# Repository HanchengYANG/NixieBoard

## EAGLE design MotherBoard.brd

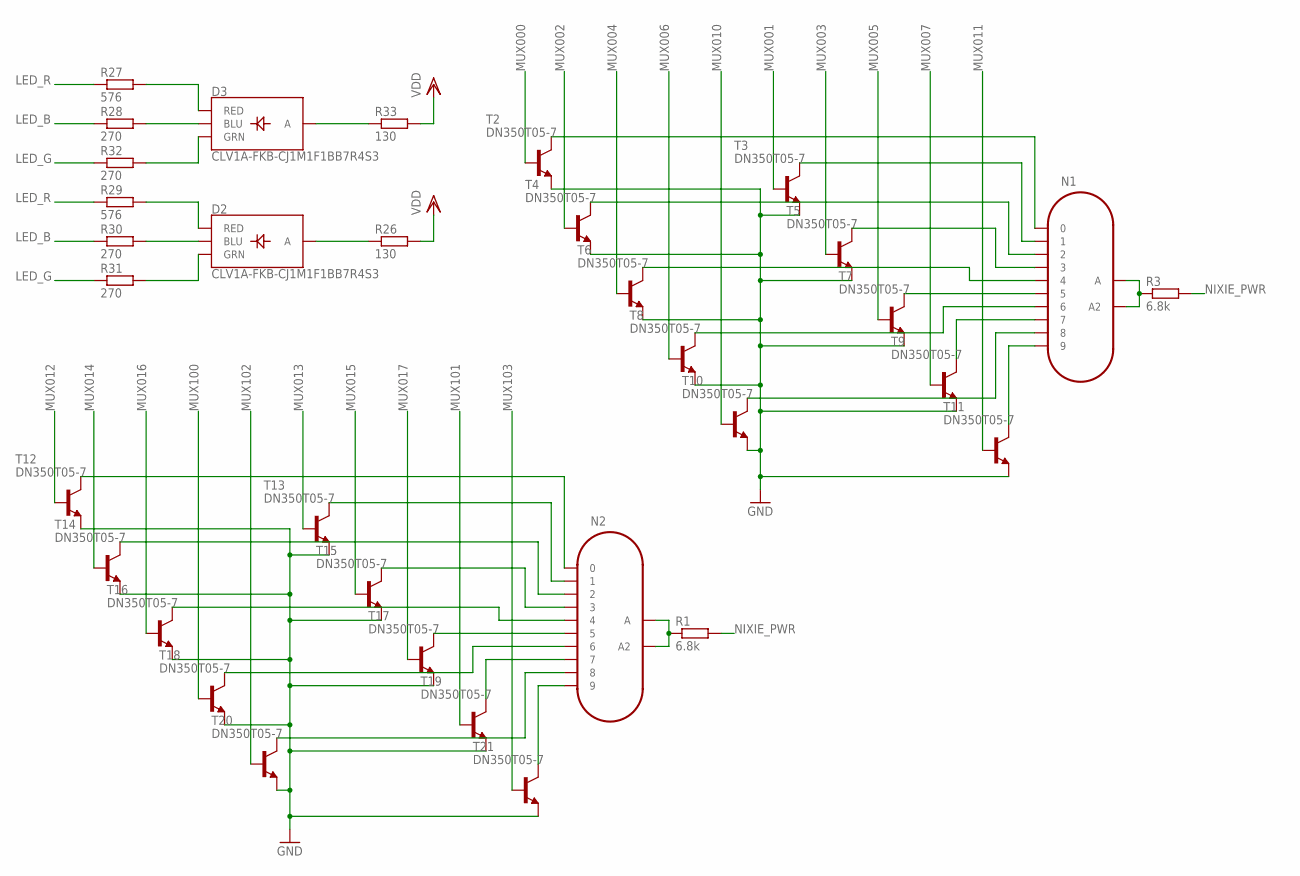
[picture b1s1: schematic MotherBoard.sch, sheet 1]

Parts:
D2, D3: CLV1A-FKB-CJ1M1F1BB7R4S3; P-LCC-4-3
N1, N2: IN-18
R1, R3: 6.8k; R0603
R26, R33: 130; R0603
R27, R29: 576; R0603
R28, R30, R31, R32: 270; R0603
T2, T3, T4, T5, T6, T7, T8, T9, T10, T11, T12, T13, T14, T15, T16, T17, T18, T19, T20, T21: DN350T05-7; SOT23-EBC

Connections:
GND: T2.E, T3.E, T4.E, T5.E, T6.E, T7.E, T8.E, T9.E, T10.E, T11.E, T12.E, T13.E, T14.E, T15.E, T16.E, T17.E, T18.E, T19.E, T20.E, T21.E; also elsewhere on the board
LED_B: R28.1, R30.1; also elsewhere on the board
LED_G: R31.1, R32.1; also elsewhere on the board
LED_R: R27.1, R29.1; also elsewhere on the board
MUX000: T2.B; also elsewhere on the board
MUX001: T3.B; also elsewhere on the board
MUX002: T4.B; also elsewhere on the board
MUX003: T5.B; also elsewhere on the board
MUX004: T6.B; also elsewhere on the board
MUX005: T7.B; also elsewhere on the board
MUX006: T8.B; also elsewhere on the board
MUX007: T9.B; also elsewhere on the board
MUX010: T10.B; also elsewhere on the board
MUX011: T11.B; also elsewhere on the board
MUX012: T12.B; also elsewhere on the board
MUX013: T13.B; also elsewhere on the board
MUX014: T14.B; also elsewhere on the board
MUX015: T15.B; also elsewhere on the board
MUX016: T16.B; also elsewhere on the board
MUX017: T17.B; also elsewhere on the board
MUX100: T18.B; also elsewhere on the board
MUX101: T19.B; also elsewhere on the board
MUX102: T20.B; also elsewhere on the board
MUX103: T21.B; also elsewhere on the board
unnamed: N2.1, T13.C
unnamed: N2.2, T14.C
unnamed: N2.3, T15.C
unnamed: N2.4, T16.C
unnamed: N1.A, N1.A2, R3.1
unnamed: N1.1, T3.C
unnamed: N1.2, T4.C
unnamed: N1.3, T5.C
unnamed: N1.4, T6.C
unnamed: N1.5, T7.C
unnamed: N1.6, T8.C
unnamed: N2.5, T17.C
unnamed: N2.6, T18.C
unnamed: N1.7, T9.C
unnamed: N1.8, T10.C
unnamed: N1.9, T11.C
unnamed: N2.7, T19.C
unnamed: N2.0, T12.C
unnamed: N2.8, T20.C
unnamed: N2.9, T21.C
unnamed: N2.A, N2.A2, R1.1
unnamed: N1.0, T2.C
unnamed: D2.4 (A), R26.1
unnamed: D2.1 (RED), R29.2
unnamed: D2.3 (BLU), R30.2
unnamed: D2.2 (GRN), R31.2
unnamed: D3.4 (A), R33.1
unnamed: D3.1 (RED), R27.2
unnamed: D3.3 (BLU), R28.2
unnamed: D3.2 (GRN), R32.2
NIXIE_PWR: R1.2, R3.2; also elsewhere on the board
VDD: R26.2, R33.2; also elsewhere on the board

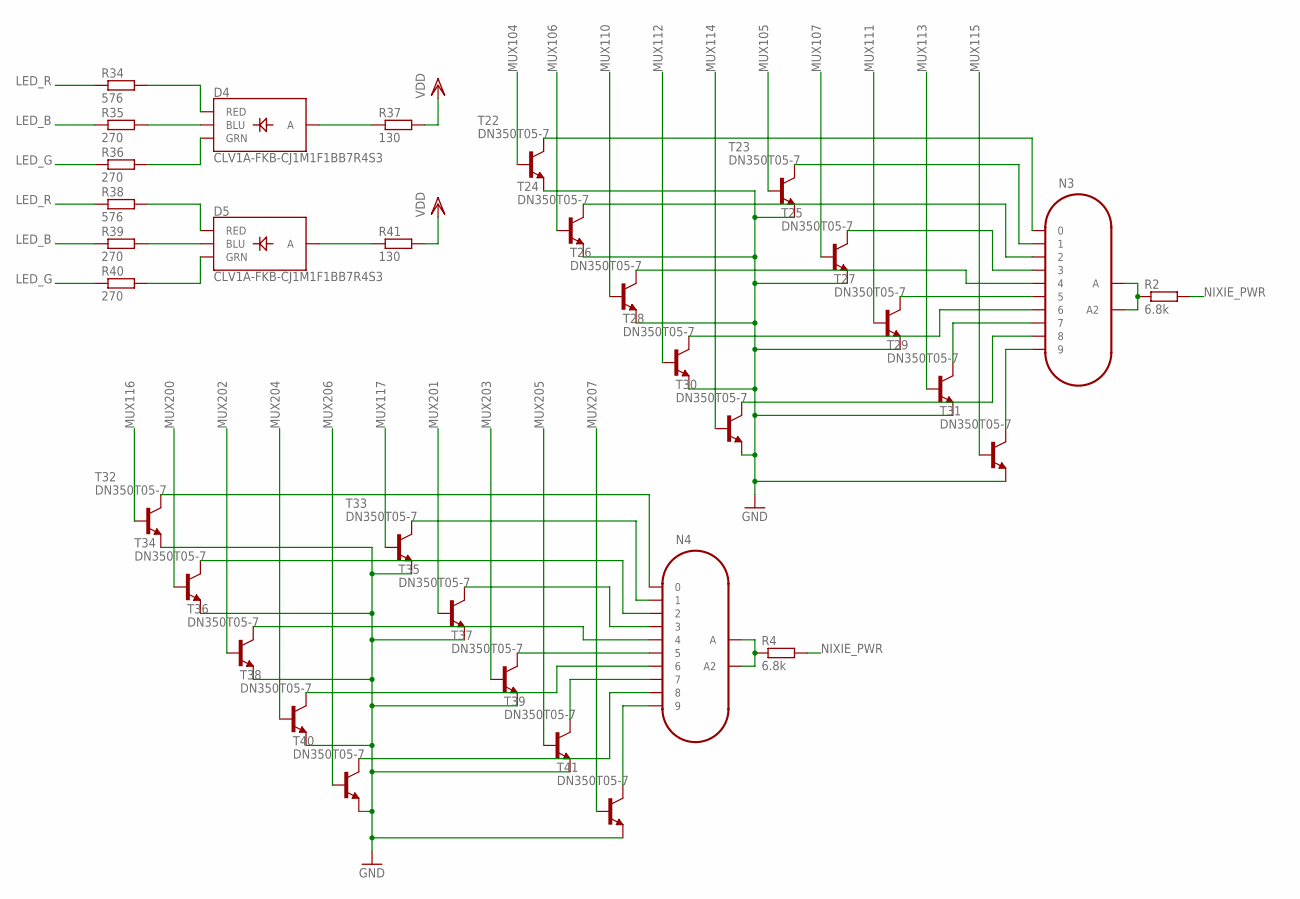
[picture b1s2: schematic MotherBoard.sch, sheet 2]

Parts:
D4, D5: CLV1A-FKB-CJ1M1F1BB7R4S3; P-LCC-4-3
N3, N4: IN-18
R2, R4: 6.8k; R0603
R34, R38: 576; R0603
R35, R36, R39, R40: 270; R0603
R37, R41: 130; R0603
T22, T23, T24, T25, T26, T27, T28, T29, T30, T31, T32, T33, T34, T35, T36, T37, T38, T39, T40, T41: DN350T05-7; SOT23-EBC

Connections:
GND: T22.E, T23.E, T24.E, T25.E, T26.E, T27.E, T28.E, T29.E, T30.E, T31.E, T32.E, T33.E, T34.E, T35.E, T36.E, T37.E, T38.E, T39.E, T40.E, T41.E; also elsewhere on the board
LED_B: R35.1, R39.1; also elsewhere on the board
LED_G: R36.1, R40.1; also elsewhere on the board
LED_R: R34.1, R38.1; also elsewhere on the board
MUX104: T22.B; also elsewhere on the board
MUX105: T23.B; also elsewhere on the board
MUX106: T24.B; also elsewhere on the board
MUX107: T25.B; also elsewhere on the board
MUX110: T26.B; also elsewhere on the board
MUX111: T27.B; also elsewhere on the board
MUX112: T28.B; also elsewhere on the board
MUX113: T29.B; also elsewhere on the board
MUX114: T30.B; also elsewhere on the board
MUX115: T31.B; also elsewhere on the board
MUX116: T32.B; also elsewhere on the board
MUX117: T33.B; also elsewhere on the board
MUX200: T34.B; also elsewhere on the board
MUX201: T35.B; also elsewhere on the board
MUX202: T36.B; also elsewhere on the board
MUX203: T37.B; also elsewhere on the board
MUX204: T38.B; also elsewhere on the board
MUX205: T39.B; also elsewhere on the board
MUX206: T40.B; also elsewhere on the board
MUX207: T41.B; also elsewhere on the board
unnamed: N3.1, T23.C
unnamed: N3.2, T24.C
unnamed: N3.3, T25.C
unnamed: N3.4, T26.C
unnamed: N3.5, T27.C
unnamed: N3.6, T28.C
unnamed: N3.7, T29.C
unnamed: N3.0, T22.C
unnamed: N3.8, T30.C
unnamed: N3.9, T31.C
unnamed: N3.A, N3.A2, R2.1
unnamed: N4.1, T33.C
unnamed: N4.2, T34.C
unnamed: N4.3, T35.C
unnamed: N4.4, T36.C
unnamed: N4.5, T37.C
unnamed: N4.6, T38.C
unnamed: N4.7, T39.C
unnamed: N4.0, T32.C
unnamed: N4.8, T40.C
unnamed: N4.9, T41.C
unnamed: N4.A, N4.A2, R4.1
unnamed: D4.4 (A), R37.1
unnamed: D4.1 (RED), R34.2
unnamed: D4.3 (BLU), R35.2
unnamed: D4.2 (GRN), R36.2
unnamed: D5.4 (A), R41.1
unnamed: D5.1 (RED), R38.2
unnamed: D5.3 (BLU), R39.2
unnamed: D5.2 (GRN), R40.2
NIXIE_PWR: R2.2, R4.2; also elsewhere on the board
VDD: R37.2, R41.2; also elsewhere on the board

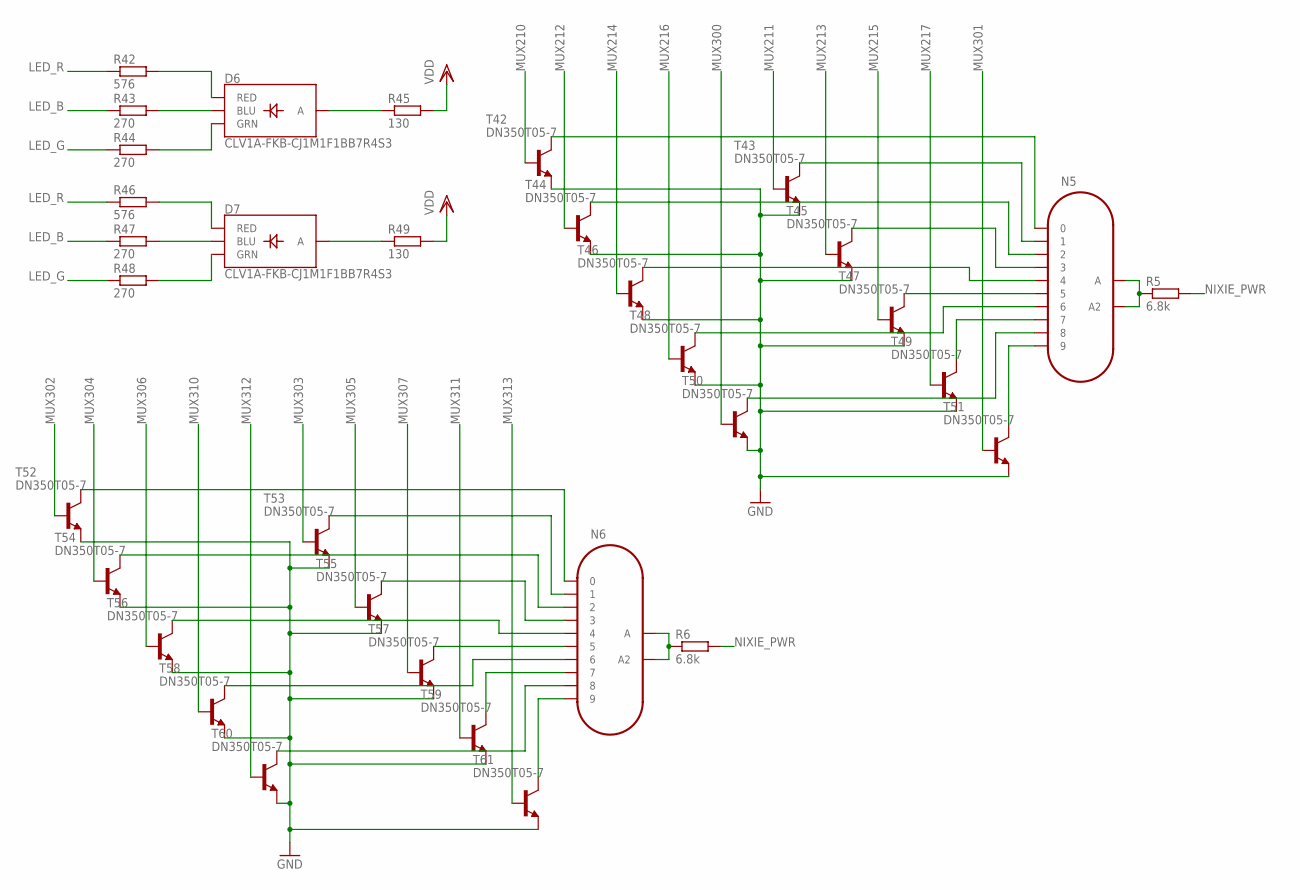
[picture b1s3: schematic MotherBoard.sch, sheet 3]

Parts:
D6, D7: CLV1A-FKB-CJ1M1F1BB7R4S3; P-LCC-4-3
N5, N6: IN-18
R5, R6: 6.8k; R0603
R42, R46: 576; R0603
R43, R44, R47, R48: 270; R0603
R45, R49: 130; R0603
T42, T43, T44, T45, T46, T47, T48, T49, T50, T51, T52, T53, T54, T55, T56, T57, T58, T59, T60, T61: DN350T05-7; SOT23-EBC

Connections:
GND: T42.E, T43.E, T44.E, T45.E, T46.E, T47.E, T48.E, T49.E, T50.E, T51.E, T52.E, T53.E, T54.E, T55.E, T56.E, T57.E, T58.E, T59.E, T60.E, T61.E; also elsewhere on the board
LED_B: R43.1, R47.1; also elsewhere on the board
LED_G: R44.1, R48.1; also elsewhere on the board
LED_R: R42.1, R46.1; also elsewhere on the board
MUX210: T42.B; also elsewhere on the board
MUX211: T43.B; also elsewhere on the board
MUX212: T44.B; also elsewhere on the board
MUX213: T45.B; also elsewhere on the board
MUX214: T46.B; also elsewhere on the board
MUX215: T47.B; also elsewhere on the board
MUX216: T48.B; also elsewhere on the board
MUX217: T49.B; also elsewhere on the board
MUX300: T50.B; also elsewhere on the board
MUX301: T51.B; also elsewhere on the board
MUX302: T52.B; also elsewhere on the board
MUX303: T53.B; also elsewhere on the board
MUX304: T54.B; also elsewhere on the board
MUX305: T55.B; also elsewhere on the board
MUX306: T56.B; also elsewhere on the board
MUX307: T57.B; also elsewhere on the board
MUX310: T58.B; also elsewhere on the board
MUX311: T59.B; also elsewhere on the board
MUX312: T60.B; also elsewhere on the board
MUX313: T61.B; also elsewhere on the board
unnamed: N5.1, T43.C
unnamed: N5.2, T44.C
unnamed: N5.3, T45.C
unnamed: N5.4, T46.C
unnamed: N5.5, T47.C
unnamed: N5.6, T48.C
unnamed: N5.7, T49.C
unnamed: N5.0, T42.C
unnamed: N5.8, T50.C
unnamed: N5.9, T51.C
unnamed: N5.A, N5.A2, R5.1
unnamed: N6.1, T53.C
unnamed: N6.2, T54.C
unnamed: N6.3, T55.C
unnamed: N6.4, T56.C
unnamed: N6.5, T57.C
unnamed: N6.6, T58.C
unnamed: N6.7, T59.C
unnamed: N6.0, T52.C
unnamed: N6.8, T60.C
unnamed: N6.9, T61.C
unnamed: N6.A, N6.A2, R6.1
unnamed: D6.4 (A), R45.1
unnamed: D6.1 (RED), R42.2
unnamed: D6.3 (BLU), R43.2
unnamed: D6.2 (GRN), R44.2
unnamed: D7.4 (A), R49.1
unnamed: D7.1 (RED), R46.2
unnamed: D7.3 (BLU), R47.2
unnamed: D7.2 (GRN), R48.2
NIXIE_PWR: R5.2, R6.2; also elsewhere on the board
VDD: R45.2, R49.2; also elsewhere on the board

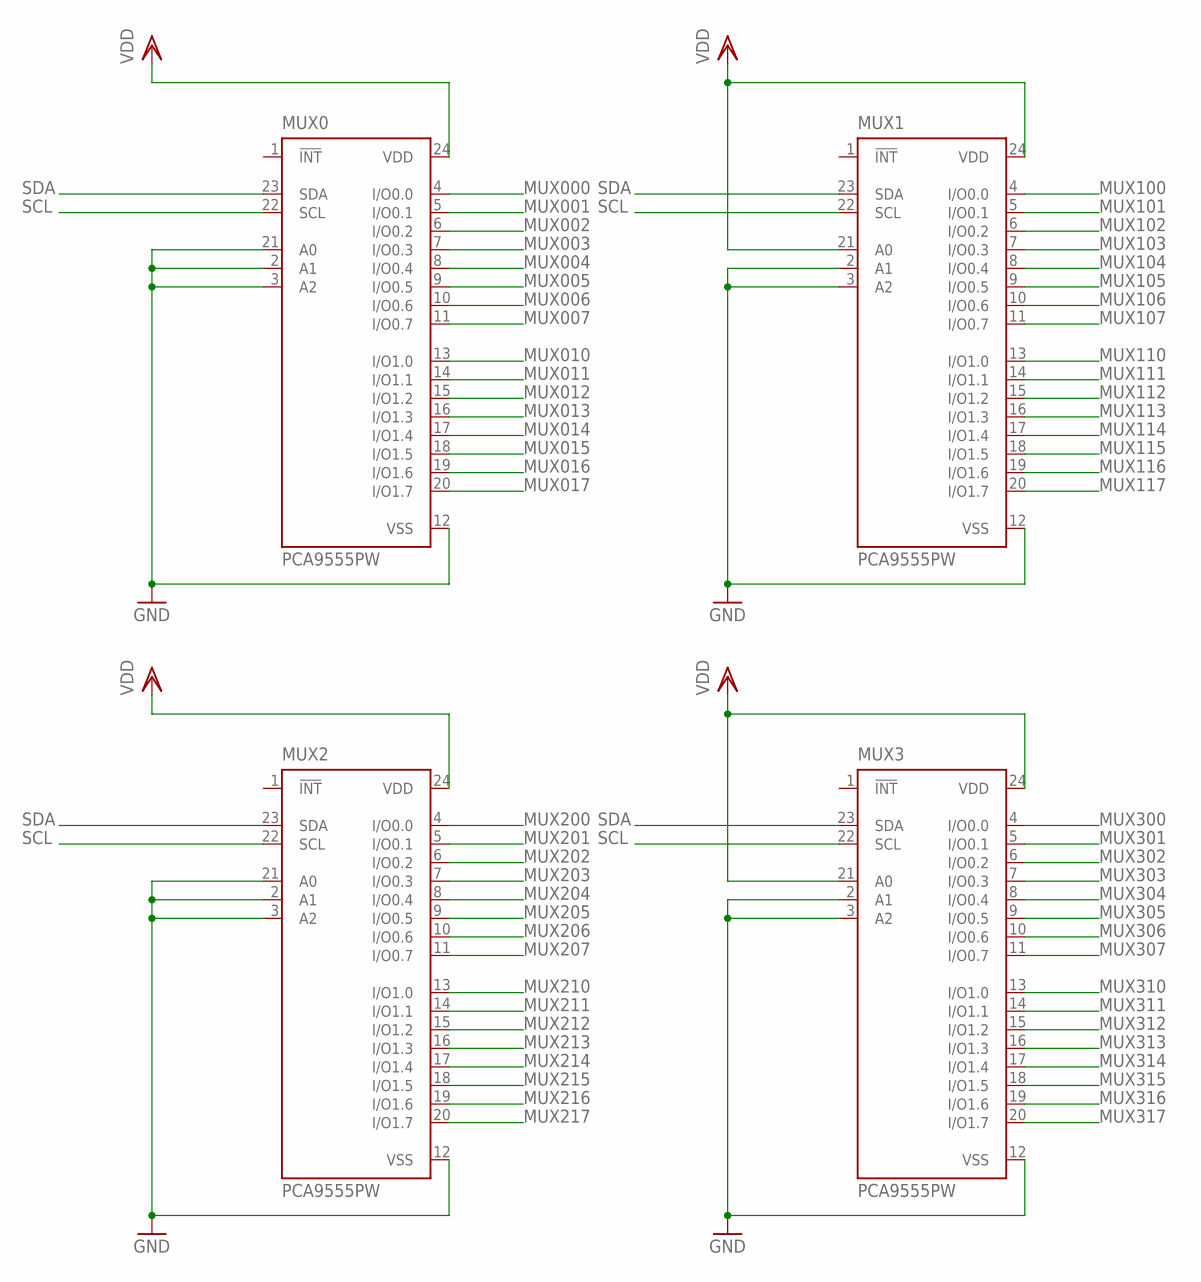
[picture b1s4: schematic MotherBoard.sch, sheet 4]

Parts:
MUX0, MUX1, MUX2, MUX3: PCA9555PW; TSSOP24

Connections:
GND: MUX0.2 (A1), MUX0.3 (A2), MUX0.12 (VSS), MUX0.21 (A0), MUX1.2 (A1), MUX1.3 (A2), MUX1.12 (VSS), MUX2.2 (A1), MUX2.3 (A2), MUX2.12 (VSS), MUX2.21 (A0), MUX3.2 (A1), MUX3.3 (A2), MUX3.12 (VSS); also elsewhere on the board
MUX000: MUX0.4 (I/O0.0); also elsewhere on the board
MUX001: MUX0.5 (I/O0.1); also elsewhere on the board
MUX002: MUX0.6 (I/O0.2); also elsewhere on the board
MUX003: MUX0.7 (I/O0.3); also elsewhere on the board
MUX004: MUX0.8 (I/O0.4); also elsewhere on the board
MUX005: MUX0.9 (I/O0.5); also elsewhere on the board
MUX006: MUX0.10 (I/O0.6); also elsewhere on the board
MUX007: MUX0.11 (I/O0.7); also elsewhere on the board
MUX010: MUX0.13 (I/O1.0); also elsewhere on the board
MUX011: MUX0.14 (I/O1.1); also elsewhere on the board
MUX012: MUX0.15 (I/O1.2); also elsewhere on the board
MUX013: MUX0.16 (I/O1.3); also elsewhere on the board
MUX014: MUX0.17 (I/O1.4); also elsewhere on the board
MUX015: MUX0.18 (I/O1.5); also elsewhere on the board
MUX016: MUX0.19 (I/O1.6); also elsewhere on the board
MUX017: MUX0.20 (I/O1.7); also elsewhere on the board
MUX100: MUX1.4 (I/O0.0); also elsewhere on the board
MUX101: MUX1.5 (I/O0.1); also elsewhere on the board
MUX102: MUX1.6 (I/O0.2); also elsewhere on the board
MUX103: MUX1.7 (I/O0.3); also elsewhere on the board
MUX104: MUX1.8 (I/O0.4); also elsewhere on the board
MUX105: MUX1.9 (I/O0.5); also elsewhere on the board
MUX106: MUX1.10 (I/O0.6); also elsewhere on the board
MUX107: MUX1.11 (I/O0.7); also elsewhere on the board
MUX110: MUX1.13 (I/O1.0); also elsewhere on the board
MUX111: MUX1.14 (I/O1.1); also elsewhere on the board
MUX112: MUX1.15 (I/O1.2); also elsewhere on the board
MUX113: MUX1.16 (I/O1.3); also elsewhere on the board
MUX114: MUX1.17 (I/O1.4); also elsewhere on the board
MUX115: MUX1.18 (I/O1.5); also elsewhere on the board
MUX116: MUX1.19 (I/O1.6); also elsewhere on the board
MUX117: MUX1.20 (I/O1.7); also elsewhere on the board
MUX200: MUX2.4 (I/O0.0); also elsewhere on the board
MUX201: MUX2.5 (I/O0.1); also elsewhere on the board
MUX202: MUX2.6 (I/O0.2); also elsewhere on the board
MUX203: MUX2.7 (I/O0.3); also elsewhere on the board
MUX204: MUX2.8 (I/O0.4); also elsewhere on the board
MUX205: MUX2.9 (I/O0.5); also elsewhere on the board
MUX206: MUX2.10 (I/O0.6); also elsewhere on the board
MUX207: MUX2.11 (I/O0.7); also elsewhere on the board
MUX210: MUX2.13 (I/O1.0); also elsewhere on the board
MUX211: MUX2.14 (I/O1.1); also elsewhere on the board
MUX212: MUX2.15 (I/O1.2); also elsewhere on the board
MUX213: MUX2.16 (I/O1.3); also elsewhere on the board
MUX214: MUX2.17 (I/O1.4); also elsewhere on the board
MUX215: MUX2.18 (I/O1.5); also elsewhere on the board
MUX216: MUX2.19 (I/O1.6); also elsewhere on the board
MUX217: MUX2.20 (I/O1.7); also elsewhere on the board
MUX300: MUX3.4 (I/O0.0); also elsewhere on the board
MUX301: MUX3.5 (I/O0.1); also elsewhere on the board
MUX302: MUX3.6 (I/O0.2); also elsewhere on the board
MUX303: MUX3.7 (I/O0.3); also elsewhere on the board
MUX304: MUX3.8 (I/O0.4); also elsewhere on the board
MUX305: MUX3.9 (I/O0.5); also elsewhere on the board
MUX306: MUX3.10 (I/O0.6); also elsewhere on the board
MUX307: MUX3.11 (I/O0.7); also elsewhere on the board
MUX310: MUX3.13 (I/O1.0); also elsewhere on the board
MUX311: MUX3.14 (I/O1.1); also elsewhere on the board
MUX312: MUX3.15 (I/O1.2); also elsewhere on the board
MUX313: MUX3.16 (I/O1.3); also elsewhere on the board
MUX314: MUX3.17 (I/O1.4)
MUX315: MUX3.18 (I/O1.5)
MUX316: MUX3.19 (I/O1.6)
MUX317: MUX3.20 (I/O1.7)
SCL: MUX0.22 (SCL), MUX1.22 (SCL), MUX2.22 (SCL), MUX3.22 (SCL); also elsewhere on the board
SDA: MUX0.23 (SDA), MUX1.23 (SDA), MUX2.23 (SDA), MUX3.23 (SDA); also elsewhere on the board
VDD: MUX0.24 (VDD), MUX1.21 (A0), MUX1.24 (VDD), MUX2.24 (VDD), MUX3.21 (A0), MUX3.24 (VDD); also elsewhere on the board

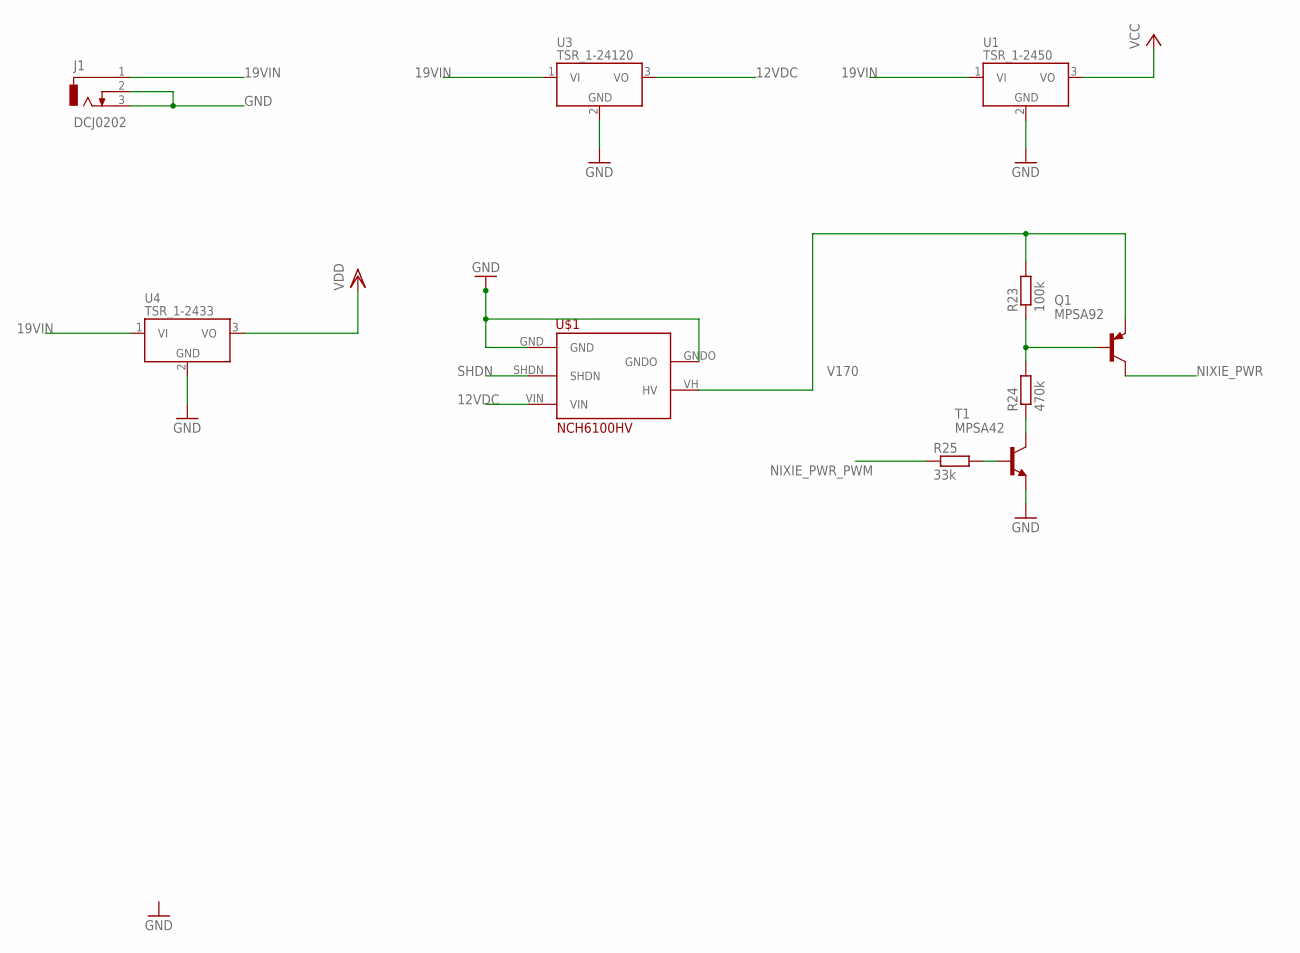
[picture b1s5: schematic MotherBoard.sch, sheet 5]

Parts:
J1: DCJ0202
Q1: MPSA92; SOT23
R23: 100k; R0603
R24: 470k; R0603
R25: 33k; R0603
T1: MPSA42; SOT23-BEC
U1: TSR_1-2450; TSR-1
U3: TSR_1-24120; TSR-1
U4: TSR_1-2433; TSR-1
U$1: NCH6100HV; NCH6100-STD

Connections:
12VDC: U3.3 (VO), U$1.VIN
19VIN: J1.1, U1.1 (VI), U3.1 (VI), U4.1 (VI)
GND: J1.2, J1.3, T1.E, U1.2 (GND), U3.2 (GND), U4.2 (GND), U$1.GND, U$1.GNDO; also elsewhere on the board
unnamed: Q1.1 (B), R23.1, R24.2
unnamed: R24.1, T1.C
unnamed: R25.2, T1.B
NIXIE_PWR: Q1.3 (C); also elsewhere on the board
NIXIE_PWR_PWM: R25.1; also elsewhere on the board
SHDN: U$1.SHDN; also elsewhere on the board
V170: Q1.2 (E), R23.2, U$1.VH (HV)
VCC: U1.3 (VO); also elsewhere on the board
VDD: U4.3 (VO); also elsewhere on the board

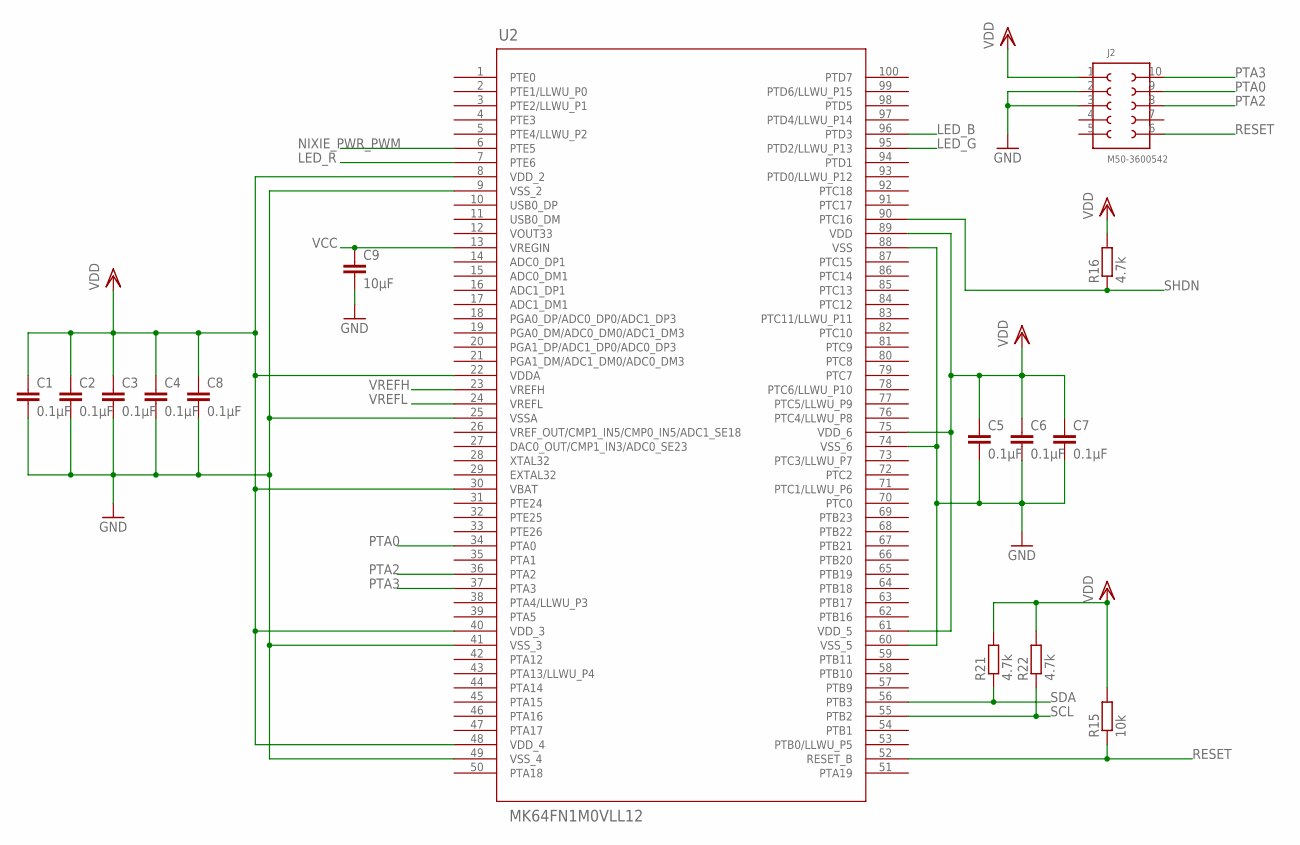
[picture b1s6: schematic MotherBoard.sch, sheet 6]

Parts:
C1, C2, C3, C4, C5, C6, C7, C8: 0.1µF; C0603
C9: 10µF; C0603
J2: M50-3600542; 621X1021021
R15: 10k; R0603
R16, R21, R22: 4.7k; R0603
U2: MK64FN1M0VLL12; LQFP-100_14X14X1.7

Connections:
GND: C1.2, C2.2, C3.2, C4.2, C5.2, C6.2, C7.2, C8.2, C9.2, J2.2, J2.3, U2.9 (VSS_2), U2.25 (VSSA), U2.41 (VSS_3), U2.49 (VSS_4), U2.60 (VSS_5), U2.74 (VSS_6), U2.88 (VSS); also elsewhere on the board
LED_B: U2.96 (PTD3); also elsewhere on the board
LED_G: U2.95 (PTD2/LLWU_P13); also elsewhere on the board
LED_R: U2.7 (PTE6); also elsewhere on the board
NIXIE_PWR_PWM: U2.6 (PTE5); also elsewhere on the board
PTA0: J2.9, U2.34 (PTA0)
PTA2: J2.8, U2.36 (PTA2)
PTA3: J2.10, U2.37 (PTA3)
RESET: J2.6, R15.1, U2.52 (RESET_B)
SCL: R22.1, U2.55 (PTB2); also elsewhere on the board
SDA: R21.1, U2.56 (PTB3); also elsewhere on the board
SHDN: R16.1, U2.90 (PTC16); also elsewhere on the board
VCC: C9.1, U2.13 (VREGIN); also elsewhere on the board
VDD: C1.1, C2.1, C3.1, C4.1, C5.1, C6.1, C7.1, C8.1, J2.1, R15.2, R16.2, R21.2, R22.2, U2.8 (VDD_2), U2.22 (VDDA), U2.30 (VBAT), U2.40 (VDD_3), U2.48 (VDD_4), U2.61 (VDD_5), U2.75 (VDD_6), U2.89 (VDD); also elsewhere on the board
VREFH: U2.23 (VREFH)
VREFL: U2.24 (VREFL)

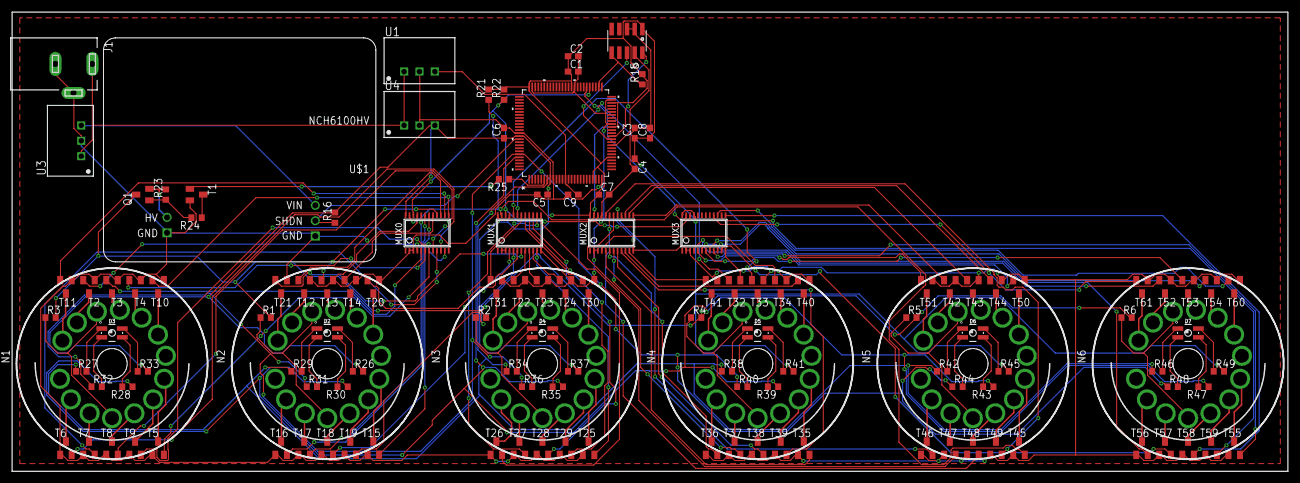
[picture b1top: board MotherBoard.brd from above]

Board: 2 copper layers, 210.8 x 75.9 mm, 131 parts (0 on the bottom side), 171 nets.

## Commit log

2017-04-04 Initial push. 6 x IN-18 nixie tubes with transistor drivers. Use NCH6100HV as power source.
2017-04-04 Add preview images.

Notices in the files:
parts and their libraries:
EAGLE-BOARD-TO-BOARD_CONNECTORS-rev16c: Copyright: Würth Elektronik
SparkFun-LED: Licensing: Creative Commons ShareAlike 4.0 International - https://creativecommons.org/licenses/by-sa/4.0
